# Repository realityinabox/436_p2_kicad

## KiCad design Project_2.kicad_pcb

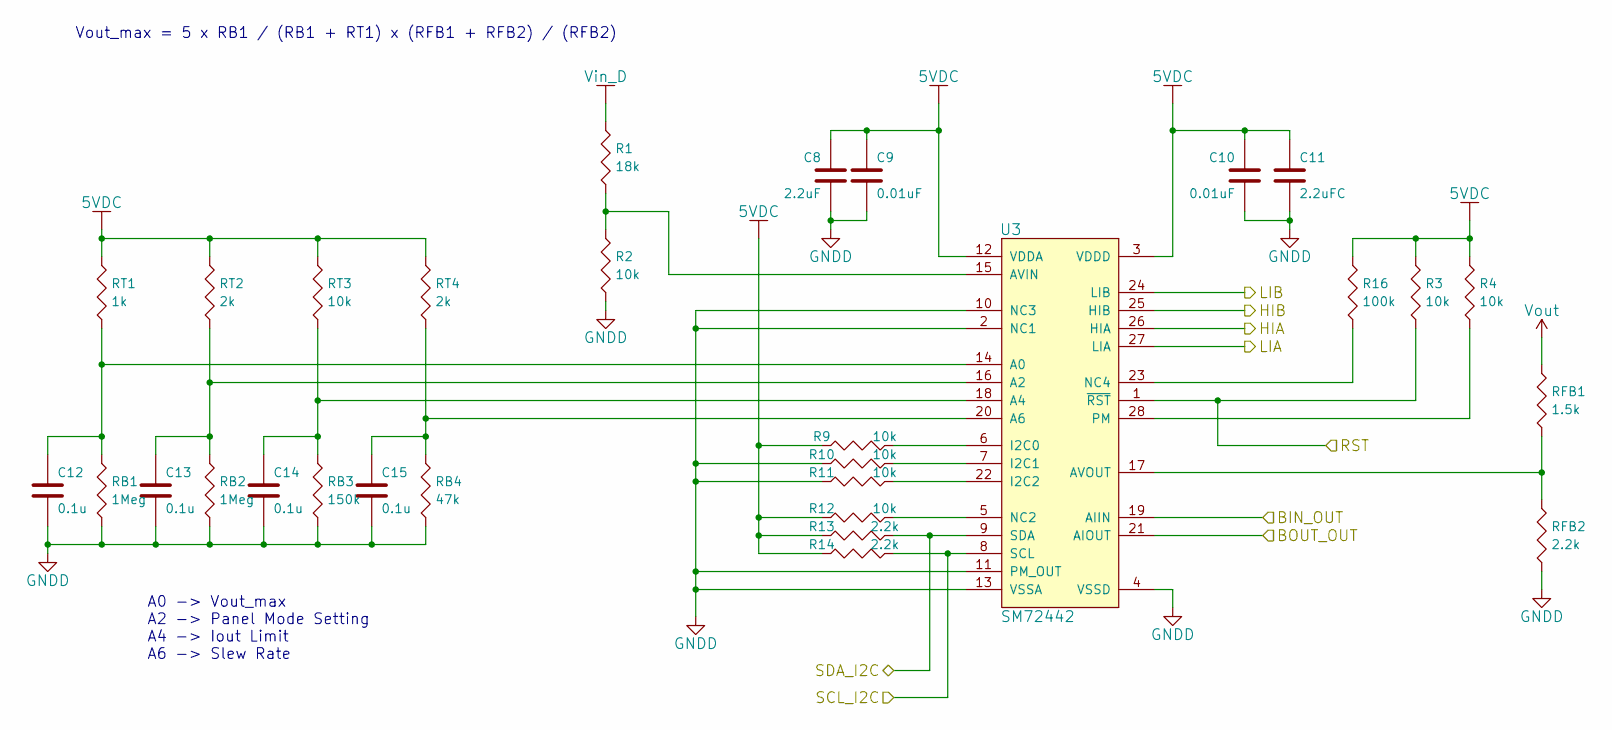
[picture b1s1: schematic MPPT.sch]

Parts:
C8: 2.2uF; C_0603_HandSoldering
C9, C10: 0.01uF; C_0603_HandSoldering
C11: 2.2uFC; C_0603_HandSoldering
C12, C13, C14, C15: 0.1u; C_0603_HandSoldering
R1: 18k; R_0603_HandSoldering
R2, R3, R4, R9, R10, R11, R12: 10k; R_0603_HandSoldering
R13, R14: 2.2k; R_0603_HandSoldering
R16: 100k; R_0603_HandSoldering
RB1, RB2: 1Meg; R_0603_HandSoldering
RB3: 150k; R_0603_HandSoldering
RB4: 47k; R_0603_HandSoldering
RFB1: 1.5k; R_0603_HandSoldering
RFB2: 2.2k; R_0603_HandSoldering
RT1: 1k; R_0603_HandSoldering
RT2, RT4: 2k; R_0603_HandSoldering
RT3: 10k; R_0603_HandSoldering
U3: SM72442; TSSOP-28_4.4x9.7mm_Pitch0.65mm

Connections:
5VDC: C8.1, C9.1, C10.1, C11.1, R3.1, R4.1, R9.1, R12.1, R13.1, R14.1, R16.1, RT1.1, RT2.1, RT3.1, RT4.1, U3.3 (VDDD), U3.12 (VDDA); also elsewhere on the board
/Connectors/BIN_OUT: U3.19 (AIIN); also elsewhere on the board
/Connectors/BOUT_OUT: U3.21 (AIOUT); also elsewhere on the board
/Connectors/RST: R3.2, U3.1 (~RST); also elsewhere on the board
/Connectors/SCL_I2C: R14.2, U3.8 (SCL); also elsewhere on the board
/Connectors/SDA_I2C: R13.2, U3.9 (SDA); also elsewhere on the board
/MPPT/HIA: U3.26 (HIA); also elsewhere on the board
/MPPT/HIB: U3.25 (HIB); also elsewhere on the board
/MPPT/LIA: U3.27 (LIA); also elsewhere on the board
/MPPT/LIB: U3.24 (LIB); also elsewhere on the board
GNDD: C8.2, C9.2, C10.2, C11.2, C12.2, C13.2, C14.2, C15.2, R2.2, R10.1, R11.1, RB1.2, RB2.2, RB3.2, RB4.2, RFB2.2, U3.2 (NC1), U3.4 (VSSD), U3.10 (NC3), U3.11 (PM_OUT), U3.13 (VSSA); also elsewhere on the board
unnamed: C12.1, RB1.1, RT1.2, U3.14 (A0)
unnamed: C13.1, RB2.1, RT2.2, U3.16 (A2)
unnamed: C14.1, RB3.1, RT3.2, U3.18 (A4)
unnamed: C15.1, RB4.1, RT4.2, U3.20 (A6)
unnamed: R1.2, R2.1, U3.15 (AVIN)
unnamed: R4.2, U3.28 (PM)
unnamed: R9.2, U3.6 (I2C0)
unnamed: R10.2, U3.7 (I2C1)
unnamed: R11.2, U3.22 (I2C2)
unnamed: R12.2, U3.5 (NC2)
unnamed: R16.2, U3.23 (NC4)
unnamed: RFB1.2, RFB2.1, U3.17 (AVOUT)
Vin_D: R1.1; also elsewhere on the board
Vout: RFB1.1; also elsewhere on the board

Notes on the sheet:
A0 -> Vout_max A2 -> Panel Mode Setting A4 -> Iout Limit A6 -> Slew Rate
Vout_max = 5 x RB1 / (RB1 + RT1) x (RFB1 + RFB2) / (RFB2)

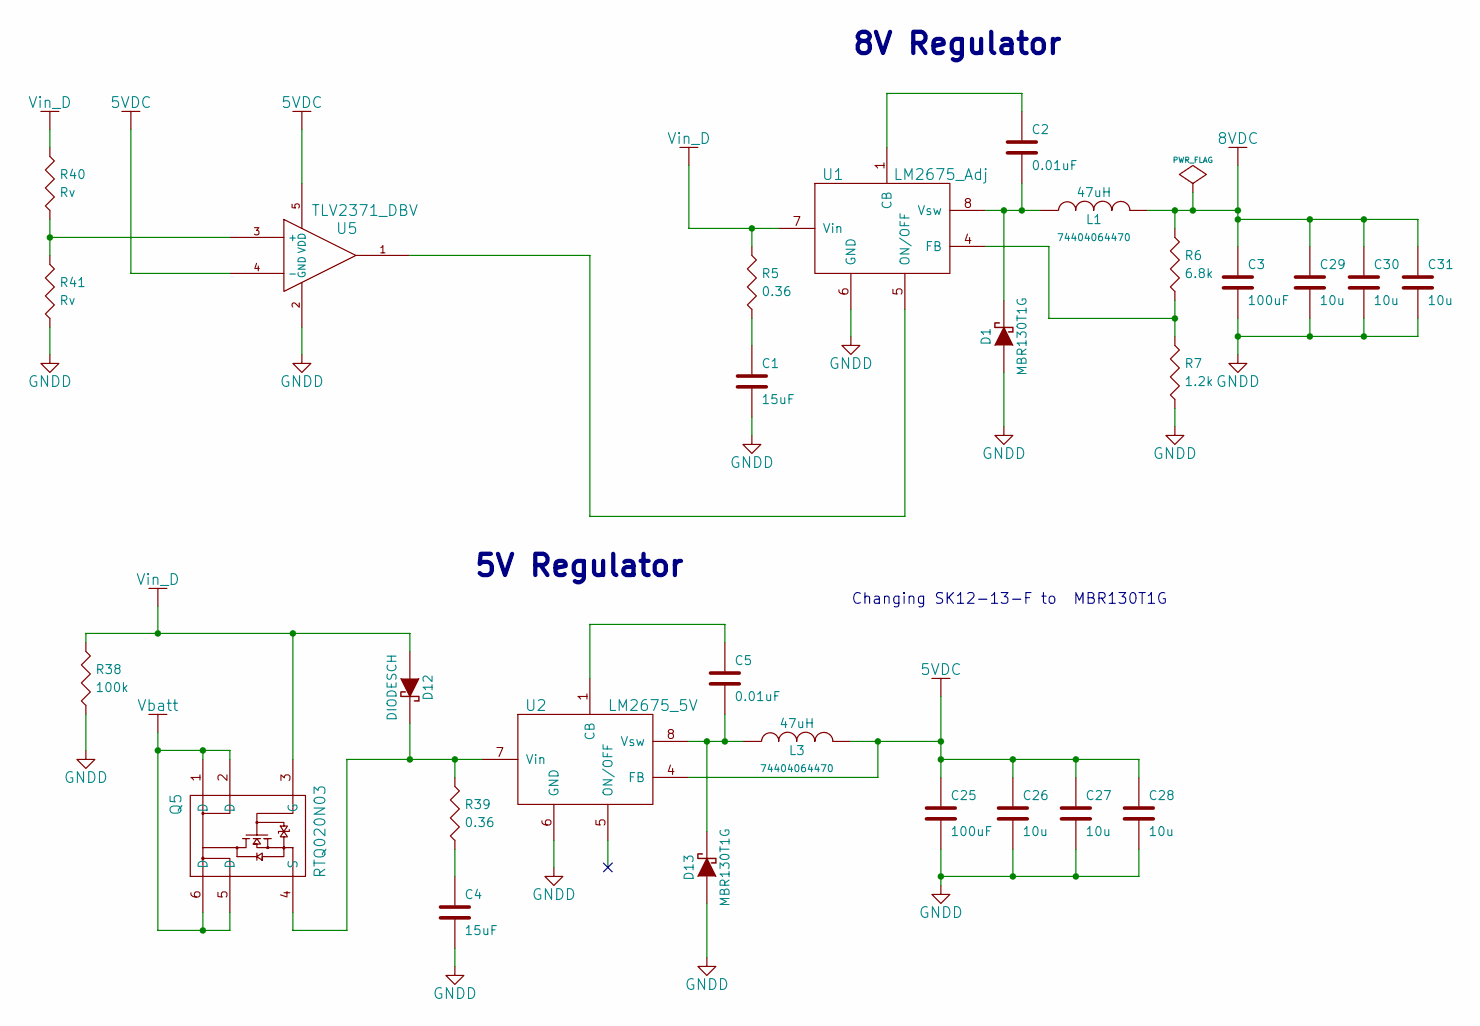
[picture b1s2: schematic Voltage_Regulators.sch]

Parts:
C1, C4: 15uF; C_0603_HandSoldering
C2, C5: 0.01uF; C_0603_HandSoldering
C3, C25: 100uF; TantalC_SizeD_EIA-7343_HandSoldering
C26, C27, C28, C29, C30, C31: 10u; C_0603_HandSoldering
D1, D13: MBR130T1G; Diode-SOD_123_Handsoldering
D12: DIODESCH; Diode-SOD_123_Handsoldering
L1, L3: 47uH; SELF-WE-TPC_M
Q5: RTQ020N03; TSOT-6-MK06A_Handsoldering
R5, R39: 0.36; R_0603_HandSoldering
R6: 6.8k; R_0603_HandSoldering
R7: 1.2k; R_0603_HandSoldering
R38: 100k; R_0603_HandSoldering
R40, R41: Rv; R_0603_HandSoldering
U1: LM2675_Adj; SOIC-8_3.9x4.9mm_Pitch1.27mm
U2: LM2675_5V; SOIC-8_3.9x4.9mm_Pitch1.27mm
U5: TLV2371_DBV; TSOT-6-MK06A_Handsoldering

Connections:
5VDC: C25.1, C26.1, C27.1, C28.1, L3.2, U2.4 (FB), U5.4 (-), U5.5 (VDD); also elsewhere on the board
8VDC: C3.1, C29.1, C30.1, C31.1, L1.2, R6.1; also elsewhere on the board
GNDD: C1.2, C3.2, C4.2, C25.2, C26.2, C27.2, C28.2, C29.2, C30.2, C31.2, D1.1 (A), D13.1 (A), R7.2, R38.2, R41.2, U1.6 (GND), U2.6 (GND), U5.2 (GND); also elsewhere on the board
unnamed: C1.1, R5.2
unnamed: C2.1, U1.1 (CB)
unnamed: C2.2, D1.2 (K), L1.1, U1.8 (Vsw)
unnamed: C4.1, R39.2
unnamed: C5.1, U2.1 (CB)
unnamed: C5.2, D13.2 (K), L3.1, U2.8 (Vsw)
unnamed: D12.2 (K), Q5.4 (S), R39.1, U2.7 (Vin)
unnamed: R6.2, R7.1, U1.4 (FB)
unnamed: R40.2, R41.1, U5.3 (+)
unnamed: U1.5 (ON/OFF), U5.1
Vbatt: Q5.1 (D), Q5.2 (D), Q5.5 (D), Q5.6 (D); also elsewhere on the board
Vin_D: D12.1 (A), Q5.3 (G), R5.1, R38.1, R40.1, U1.7 (Vin); also elsewhere on the board

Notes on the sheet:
8V Regulator
5V Regulator
Changing SK12-13-F to MBR130T1G

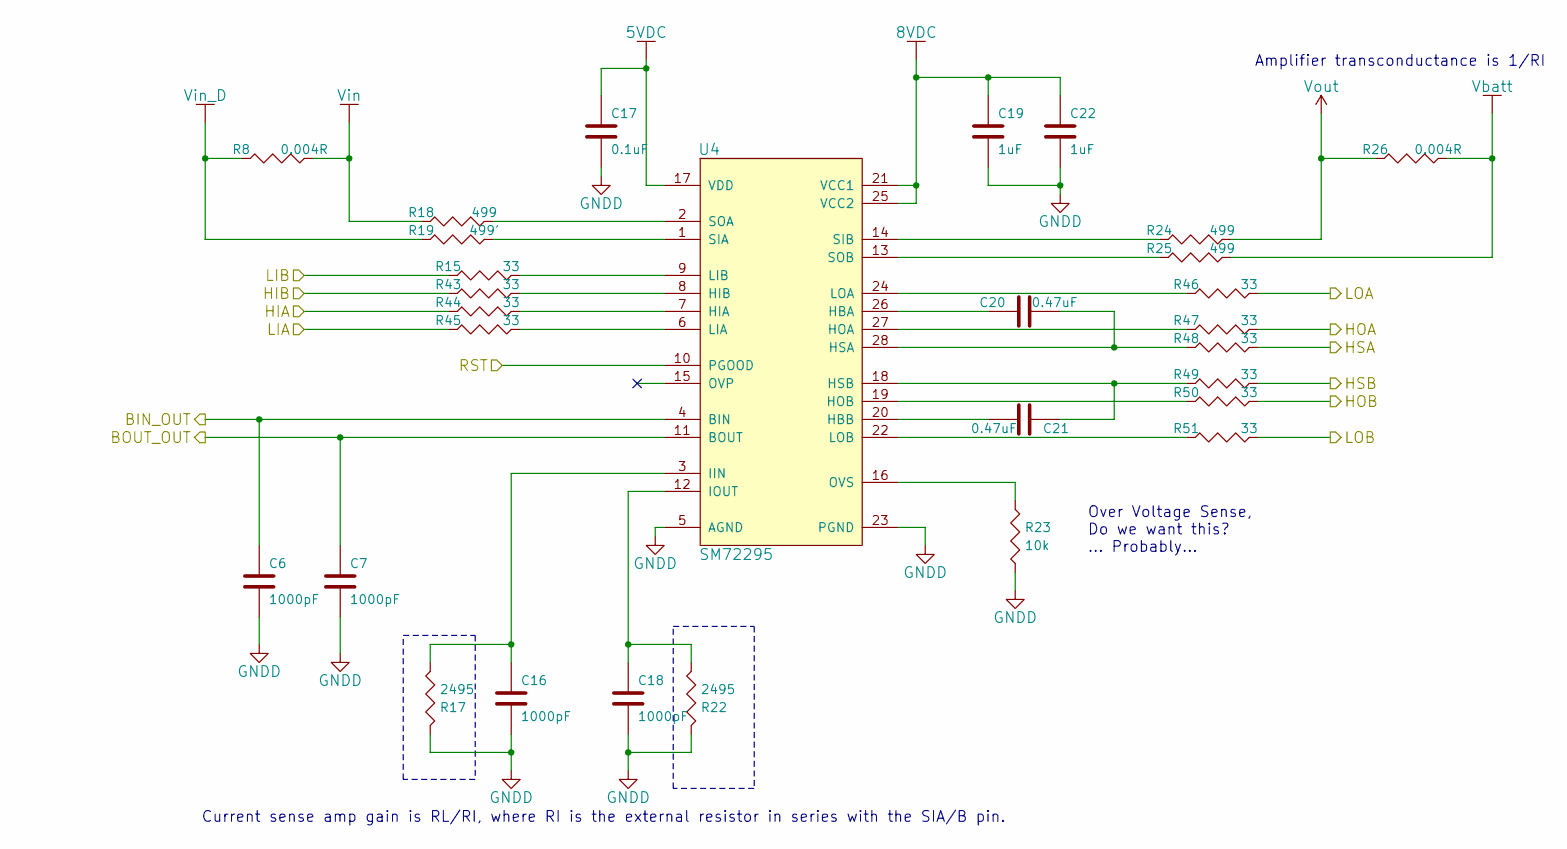
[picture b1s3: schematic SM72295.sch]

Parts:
C6, C7, C16, C18: 1000pF; C_0603_HandSoldering
C17: 0.1uF; C_0603_HandSoldering
C19, C22: 1uF; C_0603_HandSoldering
C20, C21: 0.47uF; C_0603_HandSoldering
R8, R26: 0.004R; R_0603_HandSoldering
R15, R43, R44, R45, R46, R47, R48, R49, R50, R51: 33; R_0603_HandSoldering
R17, R22: 2495; R_0603_HandSoldering
R18, R24, R25: 499; R_0603_HandSoldering
R19: 499'; R_0603_HandSoldering
R23: 10k; R_0603_HandSoldering
U4: SM72295; SOIC-28_7.5x17.9mm_Pitch1.27mm

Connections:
5VDC: C17.1, U4.17 (VDD); also elsewhere on the board
8VDC: C19.1, C22.1, U4.21 (VCC1), U4.25 (VCC2); also elsewhere on the board
/Connectors/BIN_OUT: C6.1, U4.4 (BIN); also elsewhere on the board
/Connectors/BOUT_OUT: C7.1, U4.11 (BOUT); also elsewhere on the board
/Connectors/RST: U4.10 (PGOOD); also elsewhere on the board
/HBridge/HOA: R47.2; also elsewhere on the board
/HBridge/HOB: R50.2; also elsewhere on the board
/HBridge/HSA: R48.2; also elsewhere on the board
/HBridge/HSB: R49.2; also elsewhere on the board
/HBridge/LOA: R46.2; also elsewhere on the board
/HBridge/LOB: R51.2; also elsewhere on the board
/MPPT/HIA: R44.1; also elsewhere on the board
/MPPT/HIB: R43.1; also elsewhere on the board
/MPPT/LIA: R45.1; also elsewhere on the board
/MPPT/LIB: R15.1; also elsewhere on the board
GNDD: C6.2, C7.2, C16.2, C17.2, C18.2, C19.2, C22.2, R17.1, R22.1, R23.2, U4.5 (AGND), U4.23 (PGND); also elsewhere on the board
unnamed: C16.1, R17.2, U4.3 (IIN)
unnamed: C18.1, R22.2, U4.12 (IOUT)
unnamed: C20.1, U4.26 (HBA)
unnamed: C20.2, R48.1, U4.28 (HSA)
unnamed: C21.1, R49.1, U4.18 (HSB)
unnamed: C21.2, U4.20 (HBB)
unnamed: R15.2, U4.9 (LIB)
unnamed: R18.2, U4.2 (SOA)
unnamed: R19.2, U4.1 (SIA)
unnamed: R23.1, U4.16 (OVS)
unnamed: R24.1, U4.14 (SIB)
unnamed: R25.1, U4.13 (SOB)
unnamed: R43.2, U4.8 (HIB)
unnamed: R44.2, U4.7 (HIA)
unnamed: R45.2, U4.6 (LIA)
unnamed: R46.1, U4.24 (LOA)
unnamed: R47.1, U4.27 (HOA)
unnamed: R50.1, U4.19 (HOB)
unnamed: R51.1, U4.22 (LOB)
Vbatt: R25.2, R26.2; also elsewhere on the board
Vin: R8.2, R18.1; also elsewhere on the board
Vin_D: R8.1, R19.1; also elsewhere on the board
Vout: R24.2, R26.1; also elsewhere on the board

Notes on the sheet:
Current sense amp gain is RL/RI, where RI is the external resistor in series with the SIA/B pin.
Amplifier transconductance is 1/RI
Over Voltage Sense, Do we want this? ... Probably...

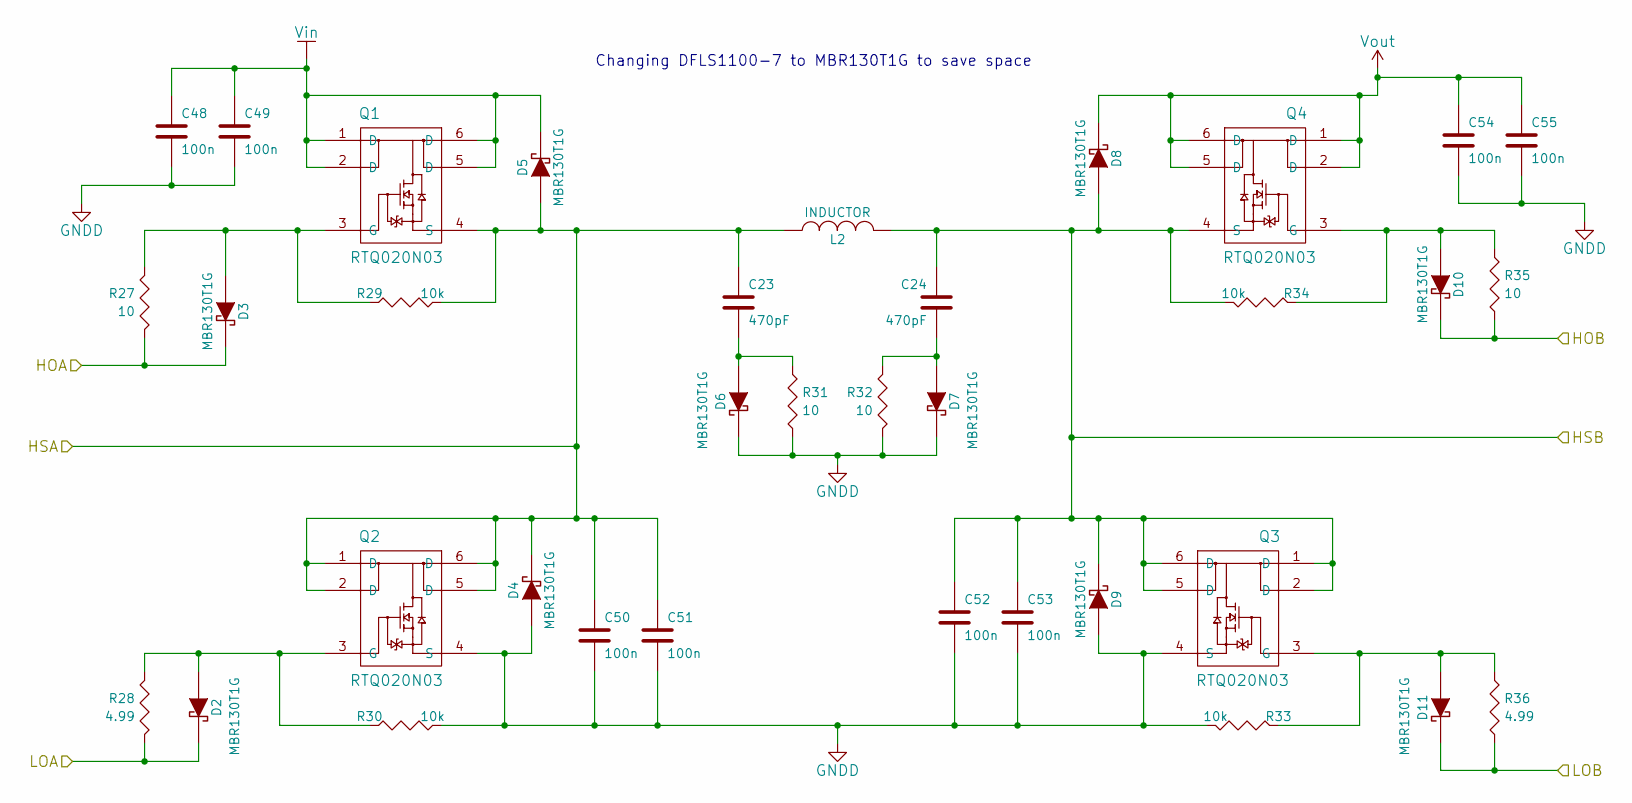
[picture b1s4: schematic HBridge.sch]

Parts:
C23, C24: 470pF; C_0603_HandSoldering
C48, C49, C50, C51, C52, C53, C54, C55: 100n
D2, D3, D4, D5, D6, D7, D8, D9, D10, D11: MBR130T1G; Diode-SOD_123_Handsoldering
L2: INDUCTOR
Q1, Q2, Q3, Q4: RTQ020N03; TSOT-6-MK06A_Handsoldering
R27, R31, R32, R35: 10; R_0603_HandSoldering
R28, R36: 4.99; R_0603_HandSoldering
R29, R30, R33, R34: 10k; R_0603_HandSoldering

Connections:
/HBridge/HOA: D3.2 (K), R27.2; also elsewhere on the board
/HBridge/HOB: D10.2 (K), R35.2; also elsewhere on the board
/HBridge/HSA: C23.1, C50.1, C51.1, D4.2 (K), D5.1 (A), L2.1, Q1.4 (S), Q2.1 (D), Q2.2 (D), Q2.5 (D), Q2.6 (D), R29.2; also elsewhere on the board
/HBridge/HSB: C24.1, C52.1, C53.1, D8.1 (A), D9.2 (K), L2.2, Q3.1 (D), Q3.2 (D), Q3.5 (D), Q3.6 (D), Q4.4 (S), R34.2; also elsewhere on the board
/HBridge/LOA: D2.2 (K), R28.2; also elsewhere on the board
/HBridge/LOB: D11.2 (K), R36.2; also elsewhere on the board
GNDD: C48.2, C49.2, C50.2, C51.2, C52.2, C53.2, C54.2, C55.2, D4.1 (A), D6.2 (K), D7.2 (K), D9.1 (A), Q2.4 (S), Q3.4 (S), R30.2, R31.2, R32.2, R33.2; also elsewhere on the board
unnamed: C23.2, D6.1 (A), R31.1
unnamed: C24.2, D7.1 (A), R32.1
unnamed: D2.1 (A), Q2.3 (G), R28.1, R30.1
unnamed: D3.1 (A), Q1.3 (G), R27.1, R29.1
unnamed: D10.1 (A), Q4.3 (G), R34.1, R35.1
unnamed: D11.1 (A), Q3.3 (G), R33.1, R36.1
Vin: C48.1, C49.1, D5.2 (K), Q1.1 (D), Q1.2 (D), Q1.5 (D), Q1.6 (D); also elsewhere on the board
Vout: C54.1, C55.1, D8.2 (K), Q4.1 (D), Q4.2 (D), Q4.5 (D), Q4.6 (D); also elsewhere on the board

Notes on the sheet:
Changing DFLS1100-7 to MBR130T1G to save space

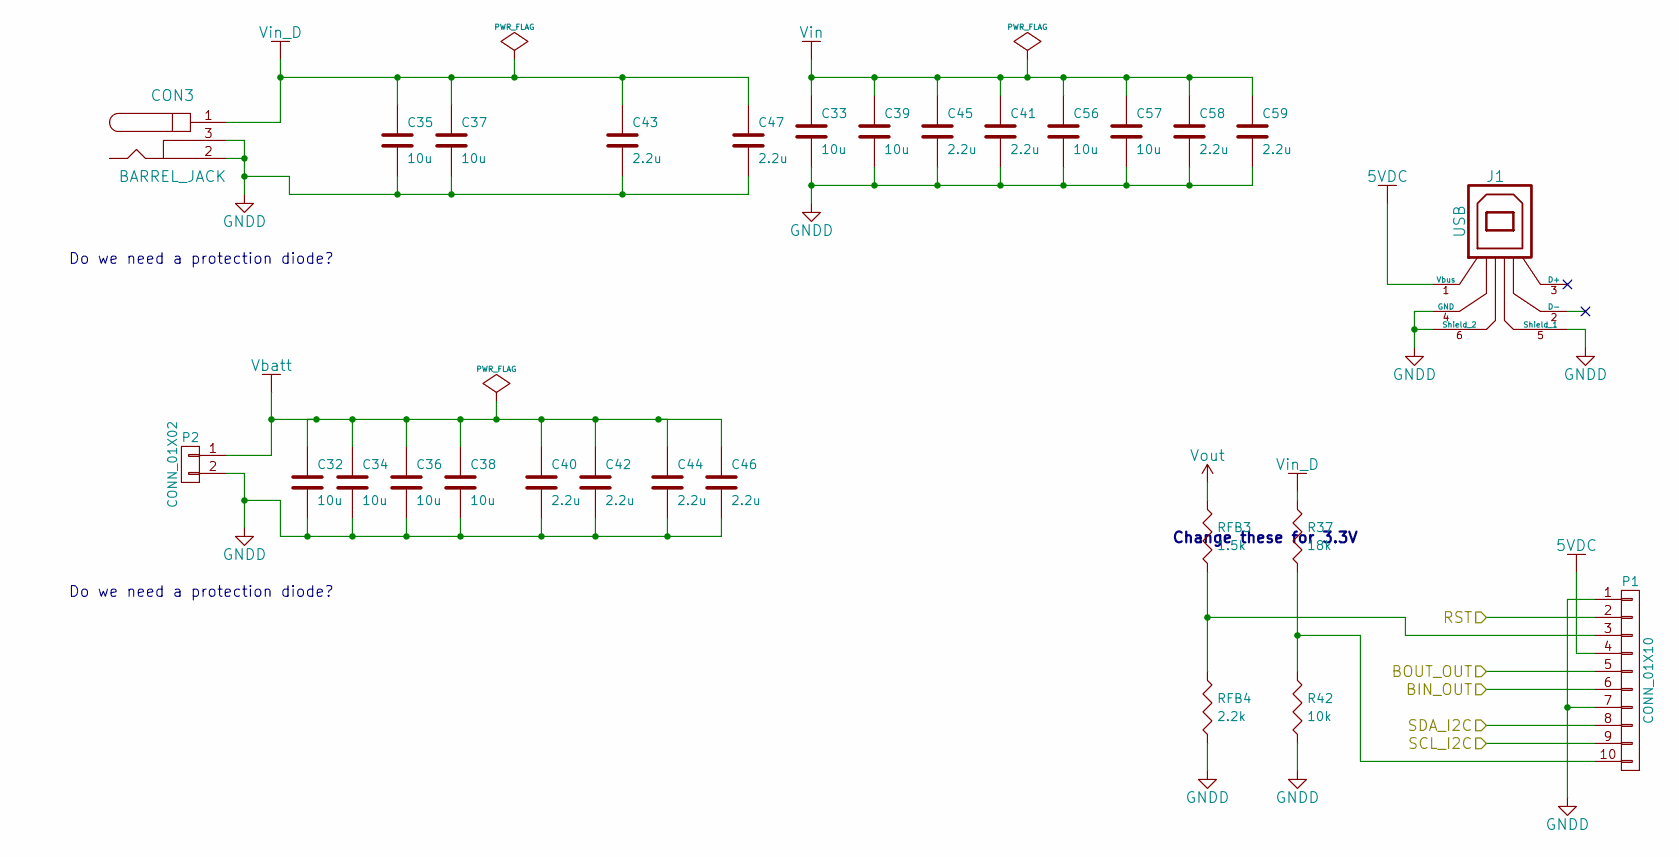
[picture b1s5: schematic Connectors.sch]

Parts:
C32, C33, C34, C35, C36, C37, C38, C39, C56, C57: 10u; C_0603_HandSoldering
C40, C41, C42, C43, C44, C45, C46, C47, C58, C59: 2.2u; C_0603_HandSoldering
CON3: BARREL_JACK
J1: USB; USB_B
P1: CONN_01X10; Socket_Strip_Straight_1x10
P2: CONN_01X02; Socket_Strip_Straight_1x02
R37: 18k; R_0603_HandSoldering
R42: 10k; R_0603_HandSoldering
RFB3: 1.5k; R_0603_HandSoldering
RFB4: 2.2k; R_0603_HandSoldering

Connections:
5VDC: J1.1 (Vbus), P1.4; also elsewhere on the board
/Connectors/BIN_OUT: P1.6; also elsewhere on the board
/Connectors/BOUT_OUT: P1.5; also elsewhere on the board
/Connectors/RST: P1.2; also elsewhere on the board
/Connectors/SCL_I2C: P1.9; also elsewhere on the board
/Connectors/SDA_I2C: P1.8; also elsewhere on the board
GNDD: C32.2, C33.2, C34.2, C35.2, C36.2, C37.2, C38.2, C39.2, C40.2, C41.2, C42.2, C43.2, C44.2, C45.2, C46.2, C47.2, C56.2, C57.2, C58.2, C59.2, CON3.2, CON3.3, J1.4 (GND), J1.5 (Shield_1), J1.6 (Shield_2), P1.1, P1.7, P2.2, R42.2, RFB4.2; also elsewhere on the board
unnamed: P1.3, RFB3.2, RFB4.1
unnamed: P1.10, R37.2, R42.1
Vbatt: C32.1, C34.1, C36.1, C38.1, C40.1, C42.1, C44.1, C46.1, P2.1; also elsewhere on the board
Vin: C33.1, C39.1, C41.1, C45.1, C56.1, C57.1, C58.1, C59.1; also elsewhere on the board
Vin_D: C35.1, C37.1, C43.1, C47.1, CON3.1, R37.1; also elsewhere on the board
Vout: RFB3.1; also elsewhere on the board

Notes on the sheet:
Do we need a protection diode?
Change these for 3.3V

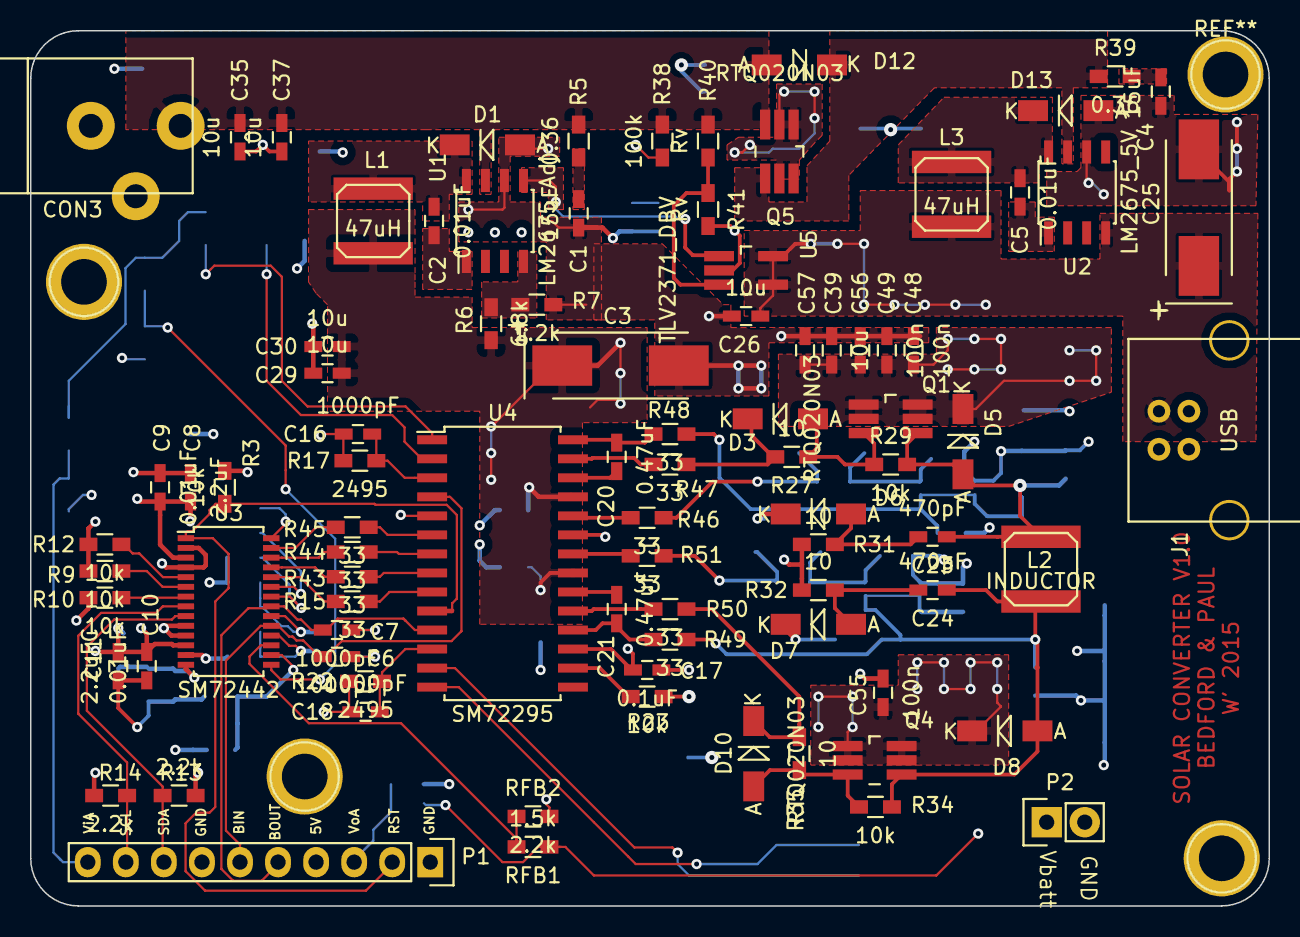
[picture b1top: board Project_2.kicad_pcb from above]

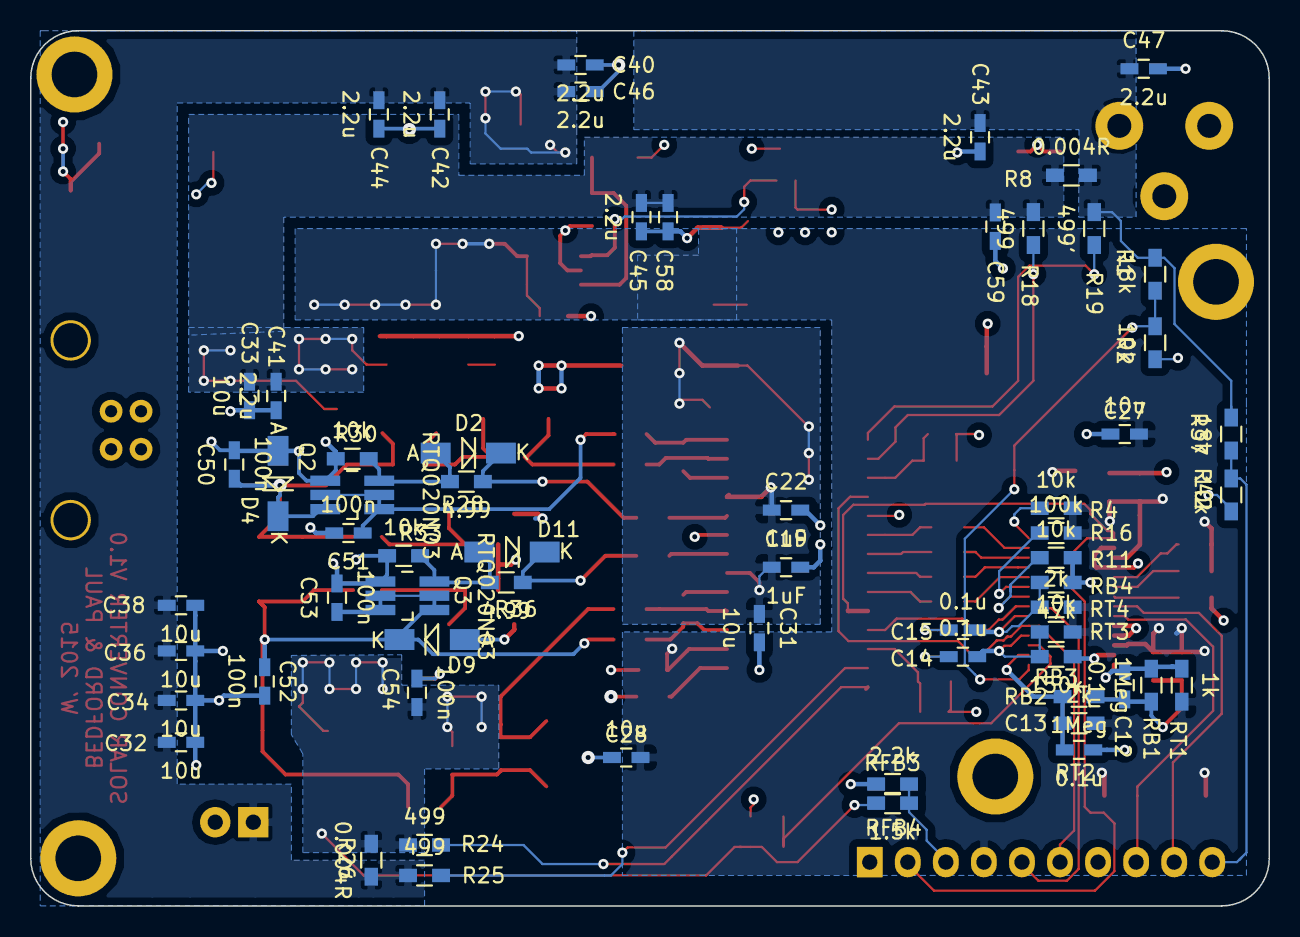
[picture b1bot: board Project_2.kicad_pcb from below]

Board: 4 copper layers, 82.7 x 58.4 mm, 150 parts (62 on the bottom side), 71 nets.

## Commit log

2015-03-10 Started placing components
2015-03-10 still trying to get initial placements done. Still need to fine-tune
2015-03-11 Started routing and dicing up power planes
2015-03-12 Routing done, prepping for DRC
2015-03-12 Cleared clearance errors. still chasing down connection issues
2015-03-13 Cleared all DRC errors.
2015-03-16 updated via placement for better ground plane continuity
